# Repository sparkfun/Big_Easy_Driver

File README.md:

SparkFun Big Easy Driver
========================

[*SparkFun Big Easy Driver (ROB-12859)*](https://www.sparkfun.com/products/12859)

This is a stepper motor driver board capable of driving bi-polar stepper motors at up to 2A/phase.

Repository Contents
-------------------

* **/Firmware** - Example Arduino sketches 
* **/Hardware** - All Eagle design files (.brd, .sch)
* **/Production** - Test bed files and production panel files

Product Versions
----------------
* [ROB-12859](https://www.sparkfun.com/products/12859)- Version 1.6. Currently available. 
* [ROB-11876](https://www.sparkfun.com/products/retired/11876)- Version 1.5. Retired. 
* [ROB-11699](https://www.sparkfun.com/products/retired/11699)- Version 1.3. Retired. 
* [ROB-10735](https://www.sparkfun.com/products/retired/10735)- Version 1.2. Retired.

Version History
---------------
* [Hw-v1.6_Fw-v1.0](https://github.com/sparkfun/Big_Easy_Driver/tree/HW-v1.6_Fw-v1.0) -GitHub tag for hardware version 1.6, firmware version 1.0.  
* [HW-v1.5](https://github.com/sparkfun/Big_Easy_Driver/tree/HW-v1.5) - GitHub tag for Hardware version 1.5. 

License Information
-------------------
The hardware is released under [Creative Commons Share-alike 3.0](http://creativecommons.org/licenses/by-sa/3.0/).  

The code is beerware; if you see me (or any other SparkFun employee) at the local, and you've found our code helpful, please buy us a round!

Distributed as-is; no warranty is given.

Getting Started Help
--------------------
There's a great [Big Easy Driver Hookup Guide](https://learn.sparkfun.com/tutorials/big-easy-driver-hookup-guide) by SparkFun.

There are six example sketches in the **/Firmware** directory. Examples 1 through 5 have hookup diagrams and explanations on the [Easy Driver Examples](http://www.schmalzhaus.com/EasyDriver/Examples/EasyDriverExamples.html) page.

_This is a collaboration with Brian Schmalz._

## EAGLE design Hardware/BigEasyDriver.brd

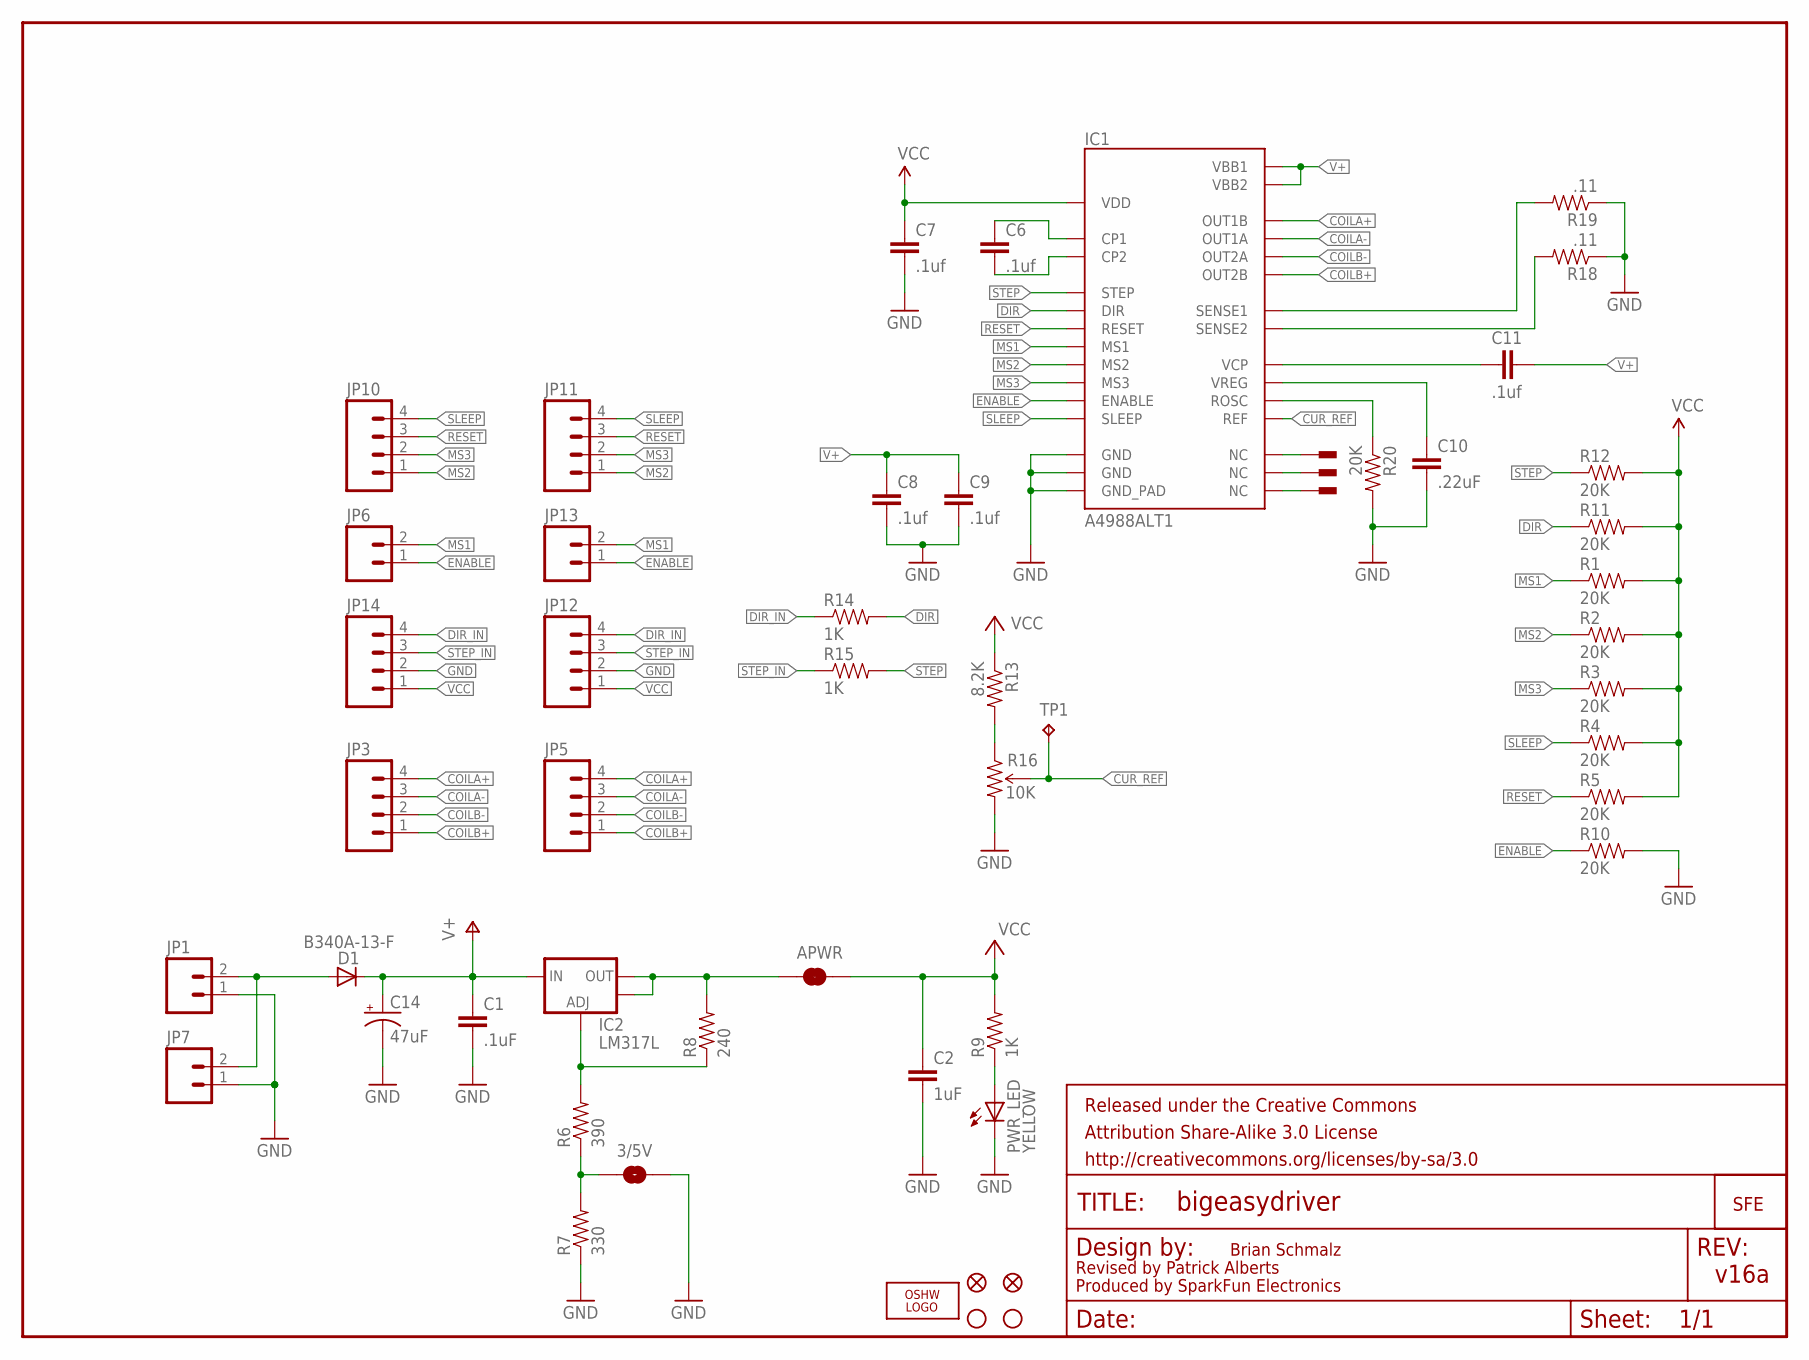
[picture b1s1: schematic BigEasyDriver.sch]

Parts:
3/5V: SOLDERJUMPERNO; SJ_2S-NO
APWR: SOLDERJUMPERTRACE; SJ_2S-TRACE
C1: .1uF; 0603-CAP
C2: 1uF; 0603-CAP
C6, C7, C8, C9, C11: .1uf; 0603-CAP
C10: .22uF; 0603-CAP
C14: 47uF; PANASONIC_D
D1: B340A-13-F; DO-214AC
FID1, FID2: FIDUCIAL1X2; FIDUCIAL-1X2
FRAME1: FRAME-LETTER; CREATIVE_COMMONS
IC1: A4988ALT1; QFN-28-5MM_ALT1
IC2: LM317L; SCHMALZHAUS_SOT89
JP1, JP6: M02PTH; 1X02
JP3, JP10, JP14: M04PTH; 1X04
JP5, JP11, JP12: M04SCREW_LOCK; SCREWTERMINAL-3.5MM-4_LOCK
JP7, JP13: M023.5MM_LOCK; SCREWTERMINAL-3.5MM-2_LOCK
JP8, JP9: STAND-OFF
LOGO1: OSHW_LOGO_FILLX0100-NT; OSHW_FILLX100_NOTEXT
PWR_LED: YELLOW; LED-0603
R1, R2, R3, R4, R5, R10, R11, R12, R20: 20K; 0603-RES
R6: 390; 0603-RES
R7: 330; 0603-RES
R8: 240; 0603-RES
R9, R14, R15: 1K; 0603-RES
R13: 8.2K; 0603-RES
R16: 10K; TRIMPOT-3MM-2
R18, R19: .11; R2010
TP1: TPPAD1-13; P1-13
U$2: LOGO-SFENEW; SFE-NEW-WEBLOGO
U$3, U$4, U$5: PAD; PAD-0.008

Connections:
5V_ALT: APWR.1, IC2.OUT, IC2.OUT@1 (OUT), R8.2
COILA+: IC1.P$21 (OUT1B), JP3.4, JP5.4
COILA-: IC1.P$24 (OUT1A), JP3.3, JP5.3
COILB+: IC1.P$1 (OUT2B), JP3.1, JP5.1
COILB-: IC1.P$26 (OUT2A), JP3.2, JP5.2
CUR_REF: IC1.P$17 (REF), R16.2 (WIPER), TP1.TP
DIR: IC1.P$19 (DIR), R11.1, R14.2
DIR_IN: JP12.4, JP14.4, R14.1
ENABLE: IC1.P$2 (ENABLE), JP6.1, JP13.1, R10.1
GND: 3/5V.2, C1.2, C2.2, C7.2, C8.2, C9.2, C10.2, C14.-, IC1.P$3 (GND), IC1.P$18 (GND), IC1.P$29 (GND_PAD), JP1.1, JP7.1, JP12.2, JP14.2, PWR_LED.C, R7.1, R10.2, R16.3 (CW), R18.1, R19.1, R20.2
MS1: IC1.P$9 (MS1), JP6.2, JP13.2, R1.1
MS2: IC1.P$10 (MS2), JP10.1, JP11.1, R2.1
MS3: IC1.P$11 (MS3), JP10.2, JP11.2, R3.1
unnamed: D1.A, JP1.2, JP7.2
unnamed: PWR_LED.A, R9.1
unnamed: R13.2, R16.1 (CCW)
unnamed: 3/5V.1, R6.1, R7.2
unnamed: IC1.P$7 (NC), U$3.P$1
unnamed: IC2.ADJ, R6.2, R8.1
unnamed: IC1.P$20 (NC), U$4.P$1
unnamed: C6.1, IC1.P$4 (CP1)
unnamed: C6.2, IC1.P$5 (CP2)
unnamed: IC1.P$25 (NC), U$5.P$1
unnamed: IC1.P$13 (ROSC), R20.1
unnamed: C10.1, IC1.P$8 (VREG)
unnamed: C11.1, IC1.P$6 (VCP)
unnamed: IC1.P$27 (SENSE2), R18.2
unnamed: IC1.P$23 (SENSE1), R19.2
RESET: IC1.P$12 (RESET), JP10.3, JP11.3, R5.1
SLEEP: IC1.P$14 (SLEEP), JP10.4, JP11.4, R4.1
STEP: IC1.P$16 (STEP), R12.1, R15.2
STEP_IN: JP12.3, JP14.3, R15.1
V+: C1.1, C8.1, C9.1, C11.2, C14.+, D1.C, IC1.P$22 (VBB1), IC1.P$28 (VBB2), IC2.IN
VCC: APWR.2, C2.1, C7.1, IC1.P$15 (VDD), JP12.1, JP14.1, R1.2, R2.2, R3.2, R4.2, R5.2, R9.2, R11.2, R12.2, R13.1

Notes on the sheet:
Brian Schmalz
Produced by SparkFun Electronics
v16a
Revised by Patrick Alberts

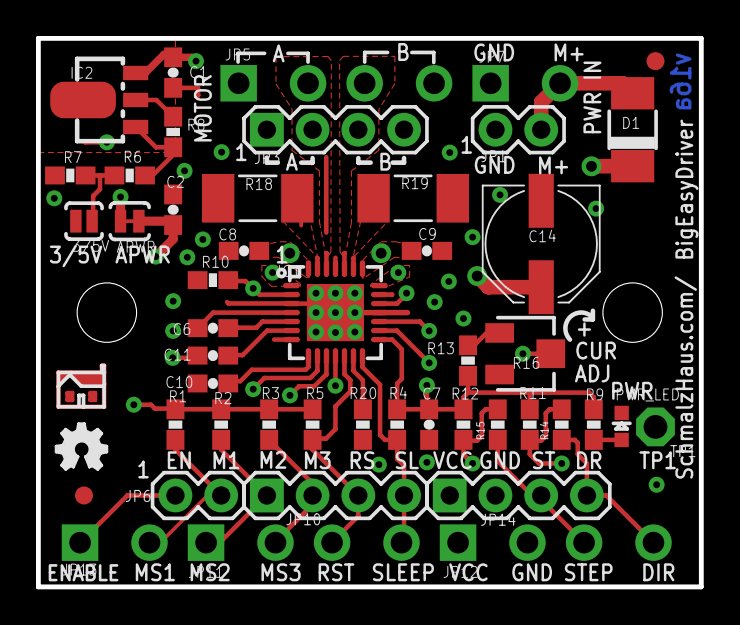
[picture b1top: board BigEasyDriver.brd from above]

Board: 4 copper layers, 36.8 x 30.5 mm, 56 parts (1 on the bottom side), 34 nets.

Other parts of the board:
U$1: SCHMALZHAUS_SMALL

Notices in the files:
Hardware/BigEasyDriver.sch:
Changed license from CC by 3.0 to CC by-sa 3.0
parts and their libraries:
SparkFun-Aesthetics: Licensing: CC v3.0 Share-Alike You are welcome to use this library for commercial purposes.
SparkFun-Aesthetics: Released under the Creative Commons Attribution Share-Alike 3.0 License
SparkFun-Aesthetics: Released under the Creative Commons
